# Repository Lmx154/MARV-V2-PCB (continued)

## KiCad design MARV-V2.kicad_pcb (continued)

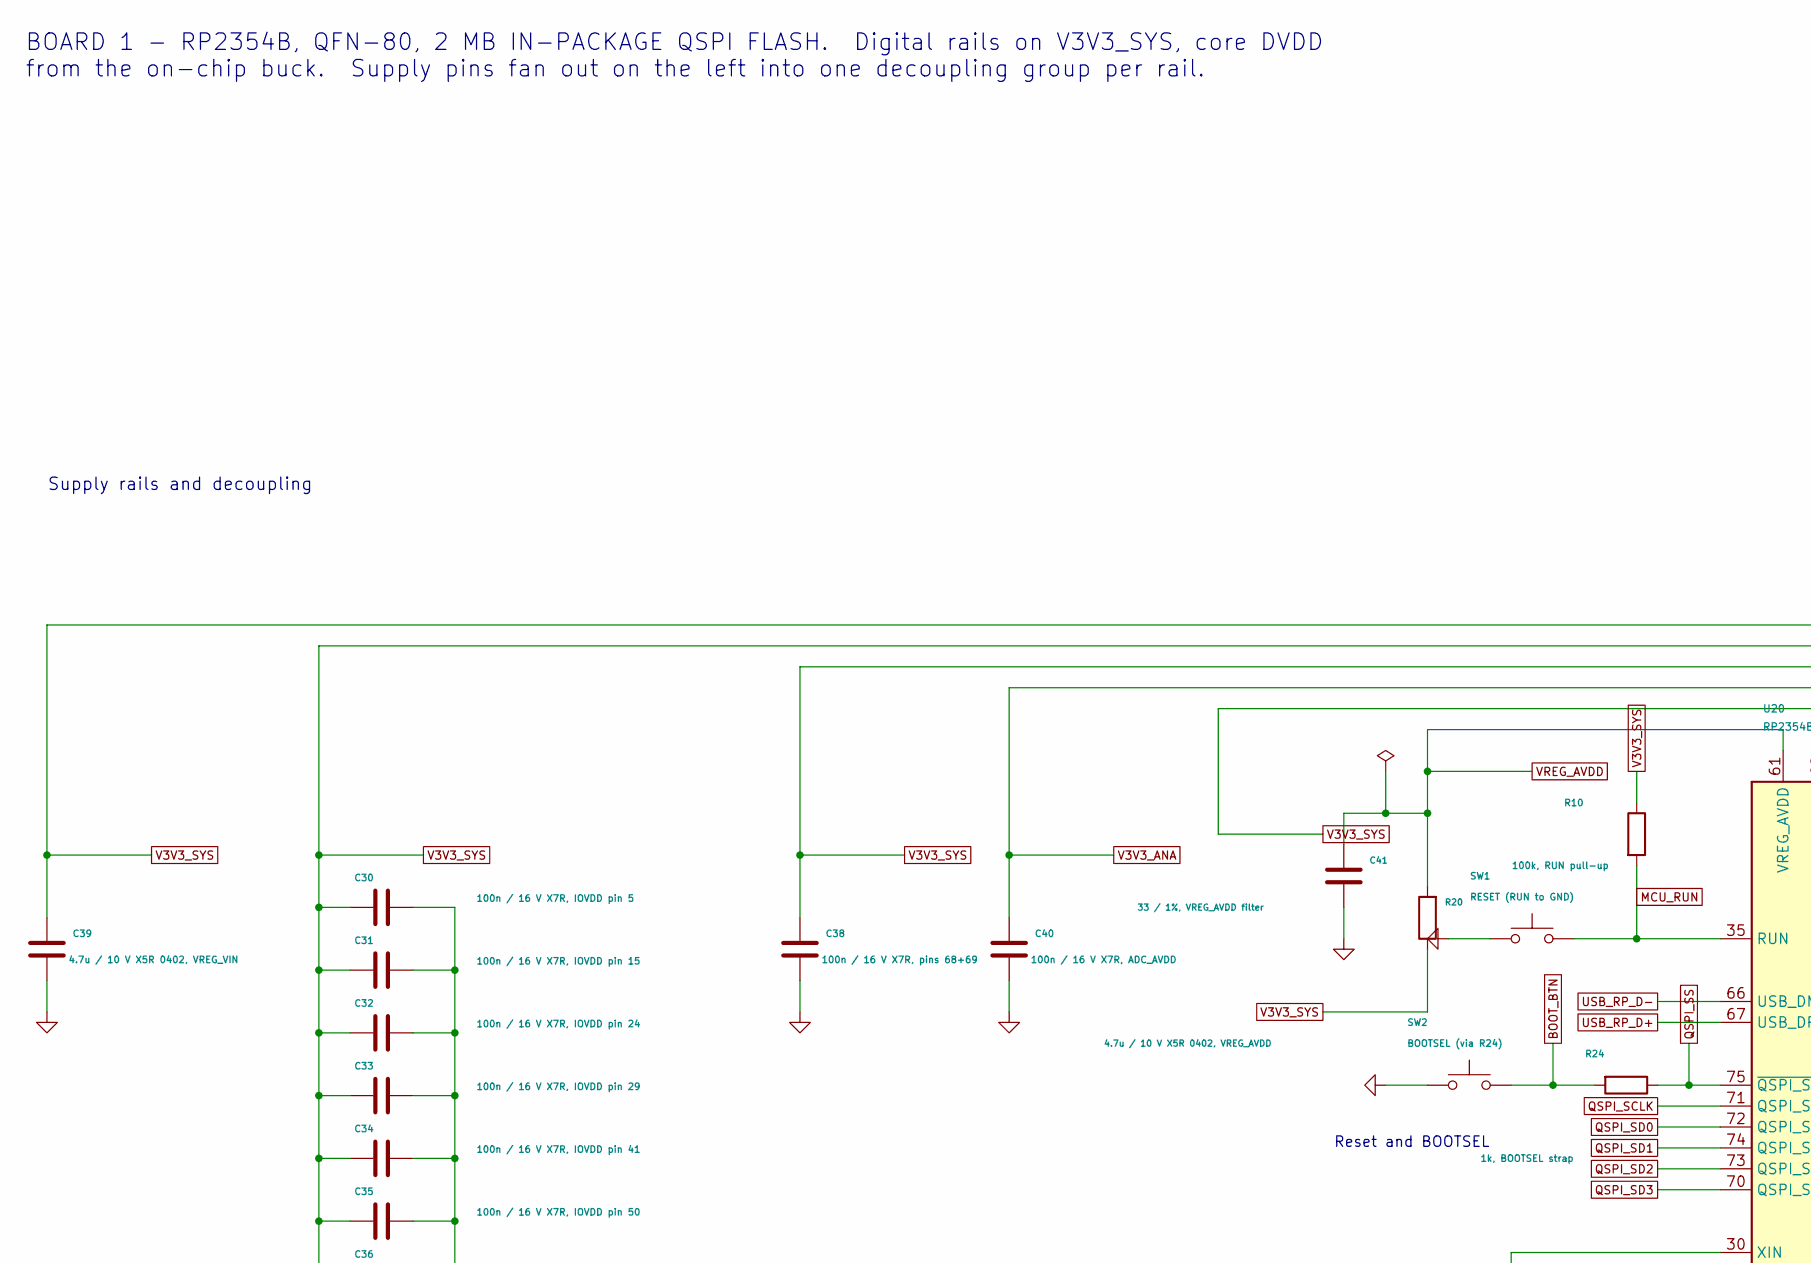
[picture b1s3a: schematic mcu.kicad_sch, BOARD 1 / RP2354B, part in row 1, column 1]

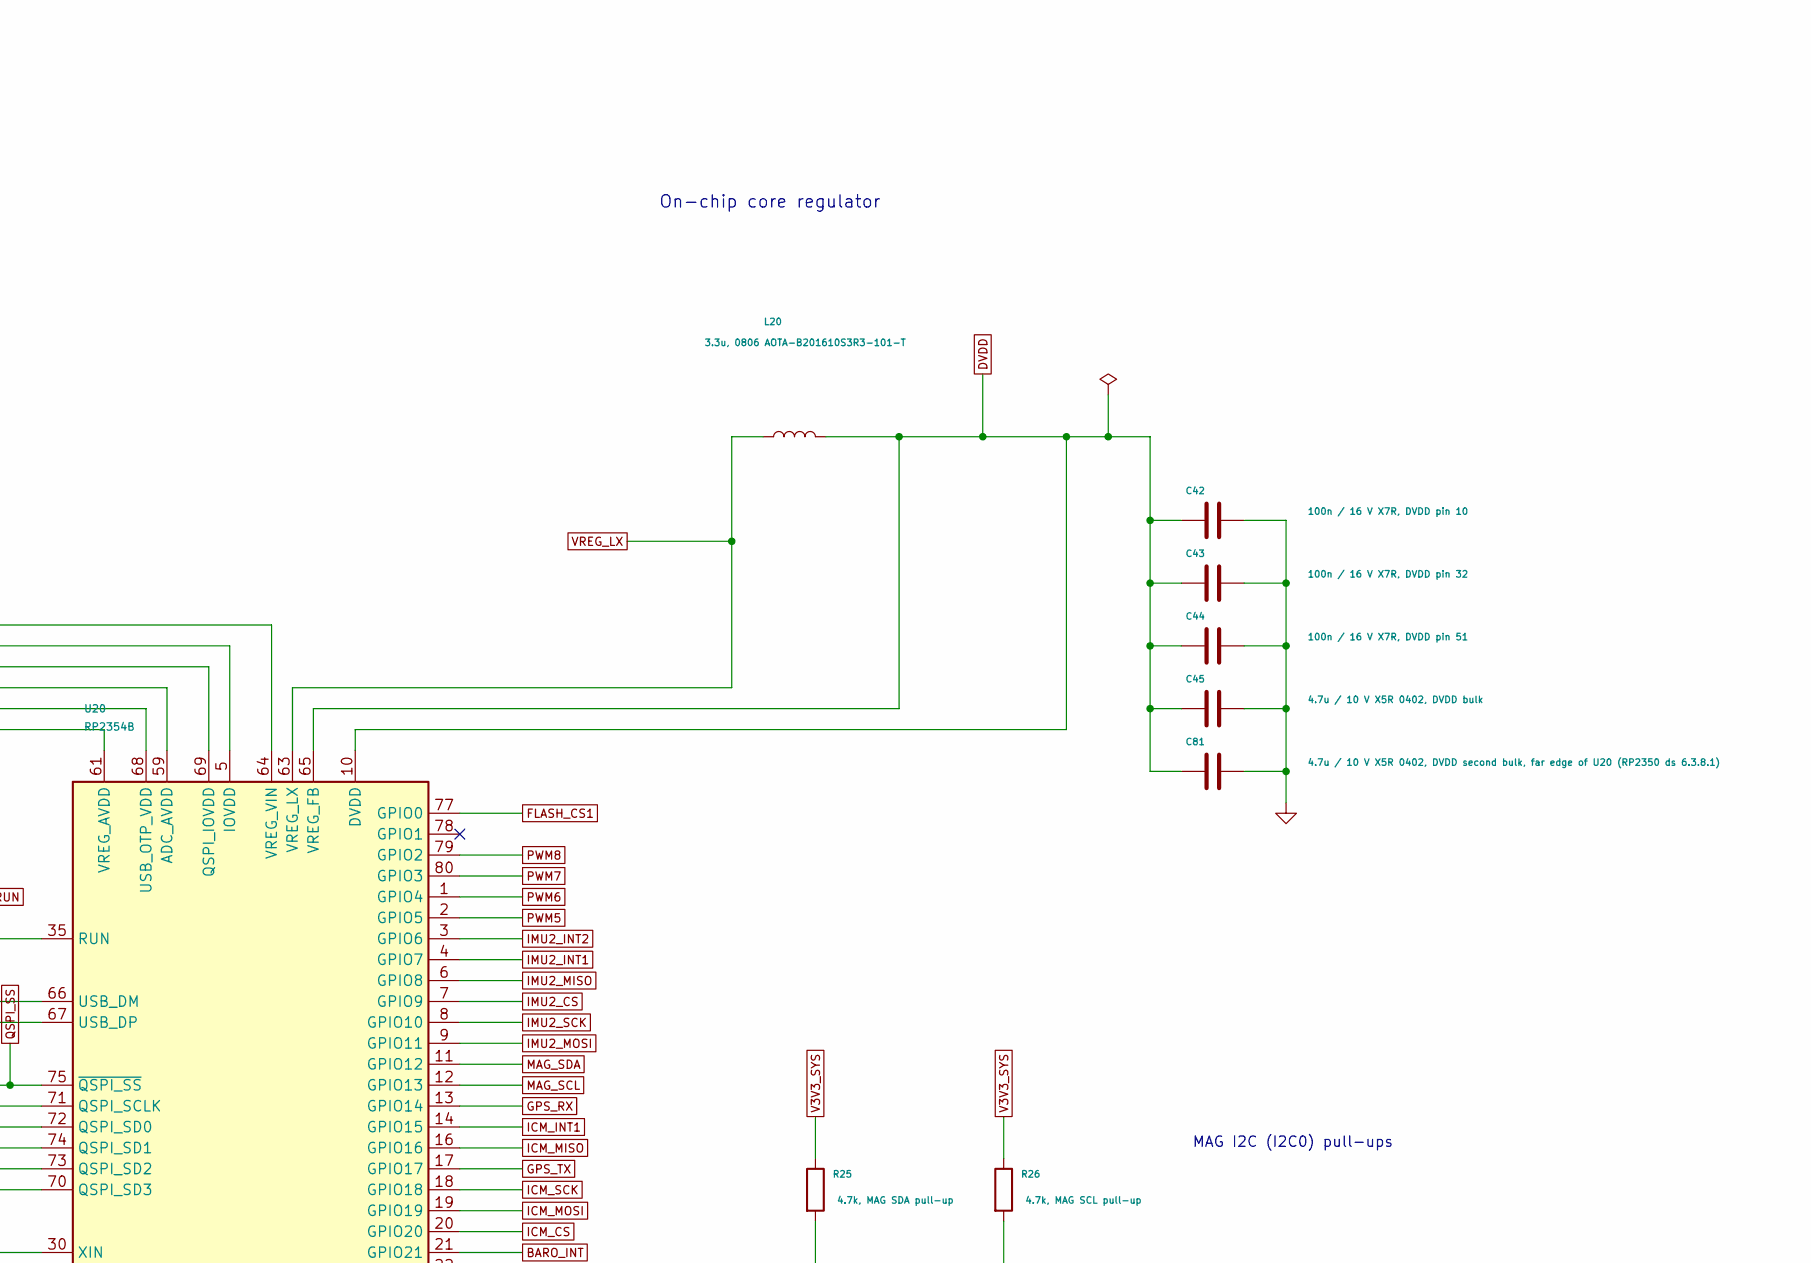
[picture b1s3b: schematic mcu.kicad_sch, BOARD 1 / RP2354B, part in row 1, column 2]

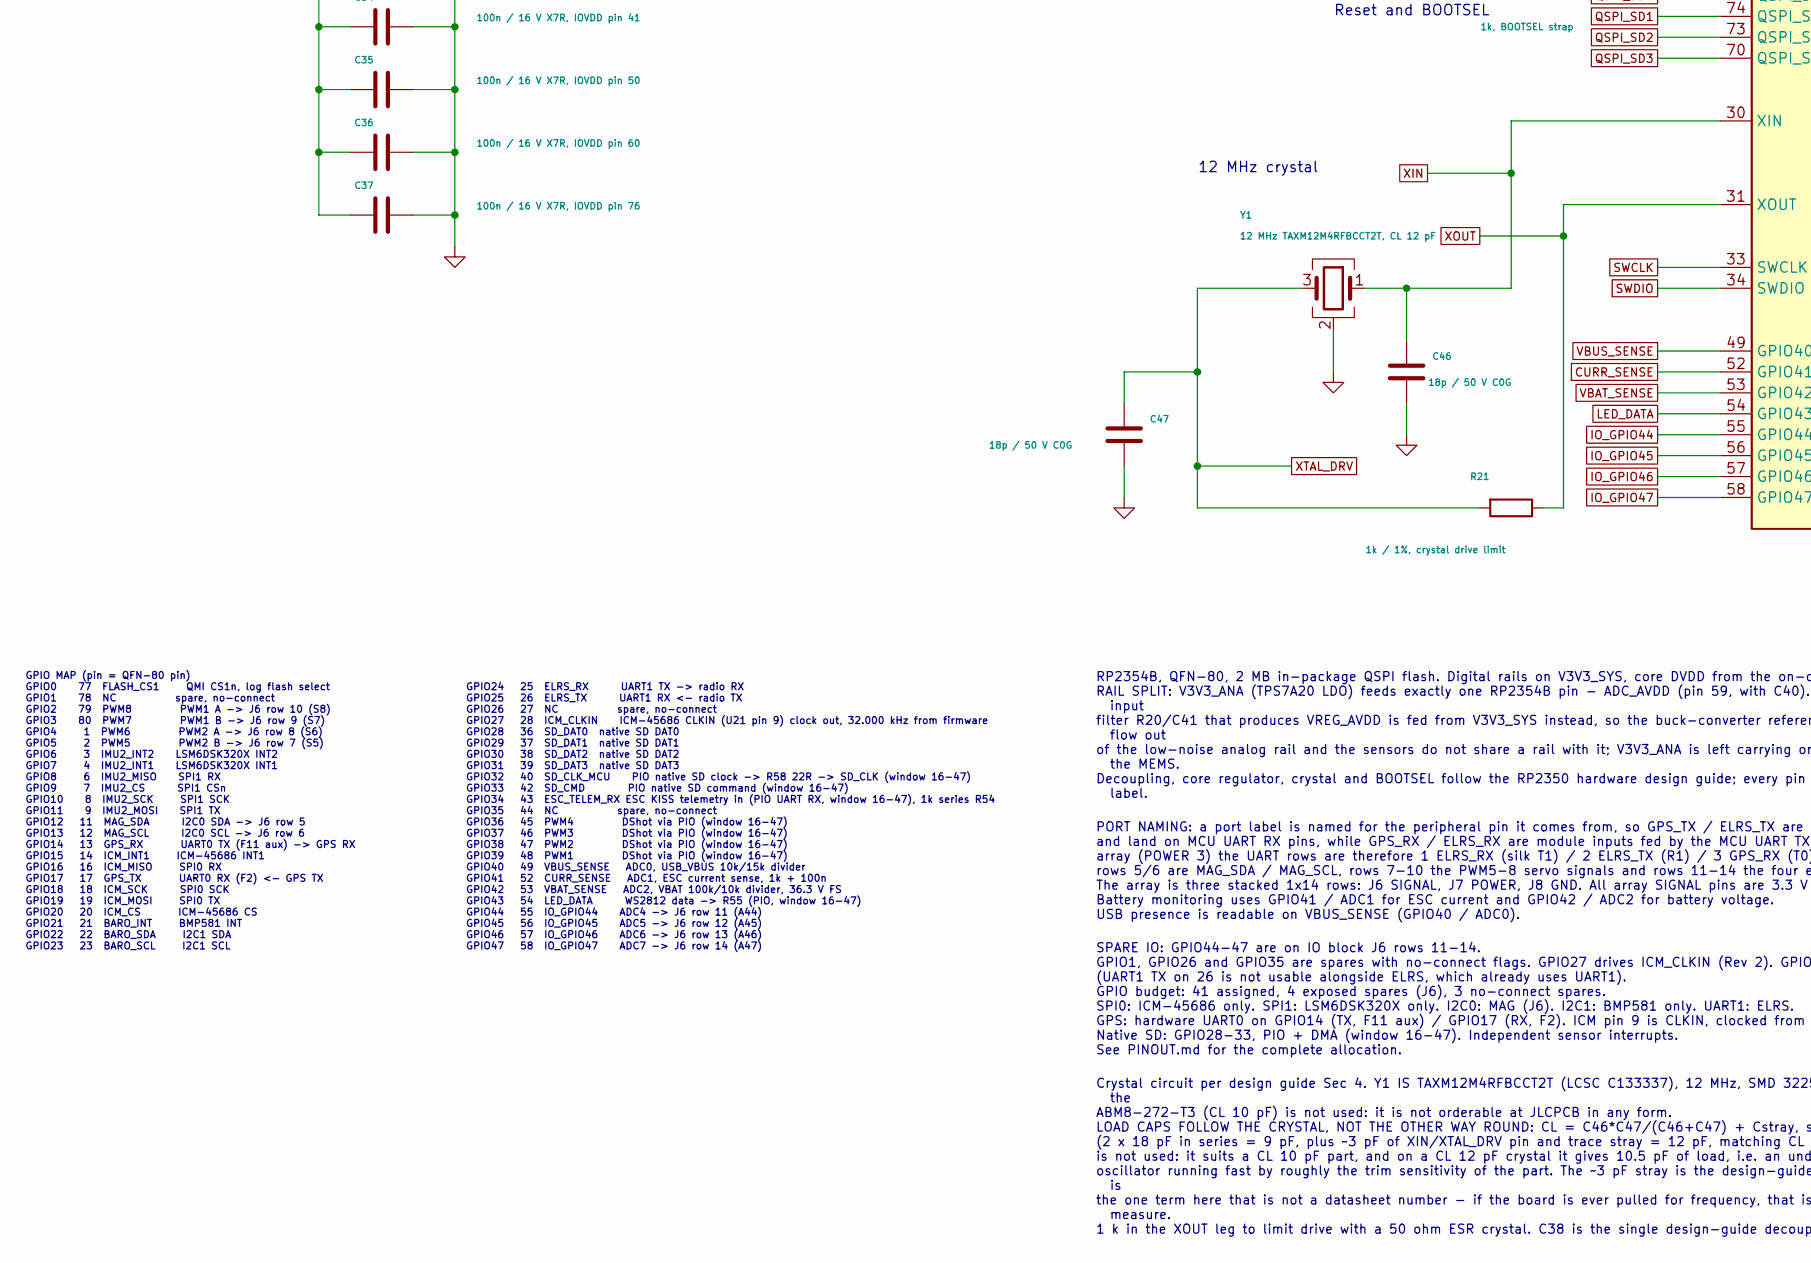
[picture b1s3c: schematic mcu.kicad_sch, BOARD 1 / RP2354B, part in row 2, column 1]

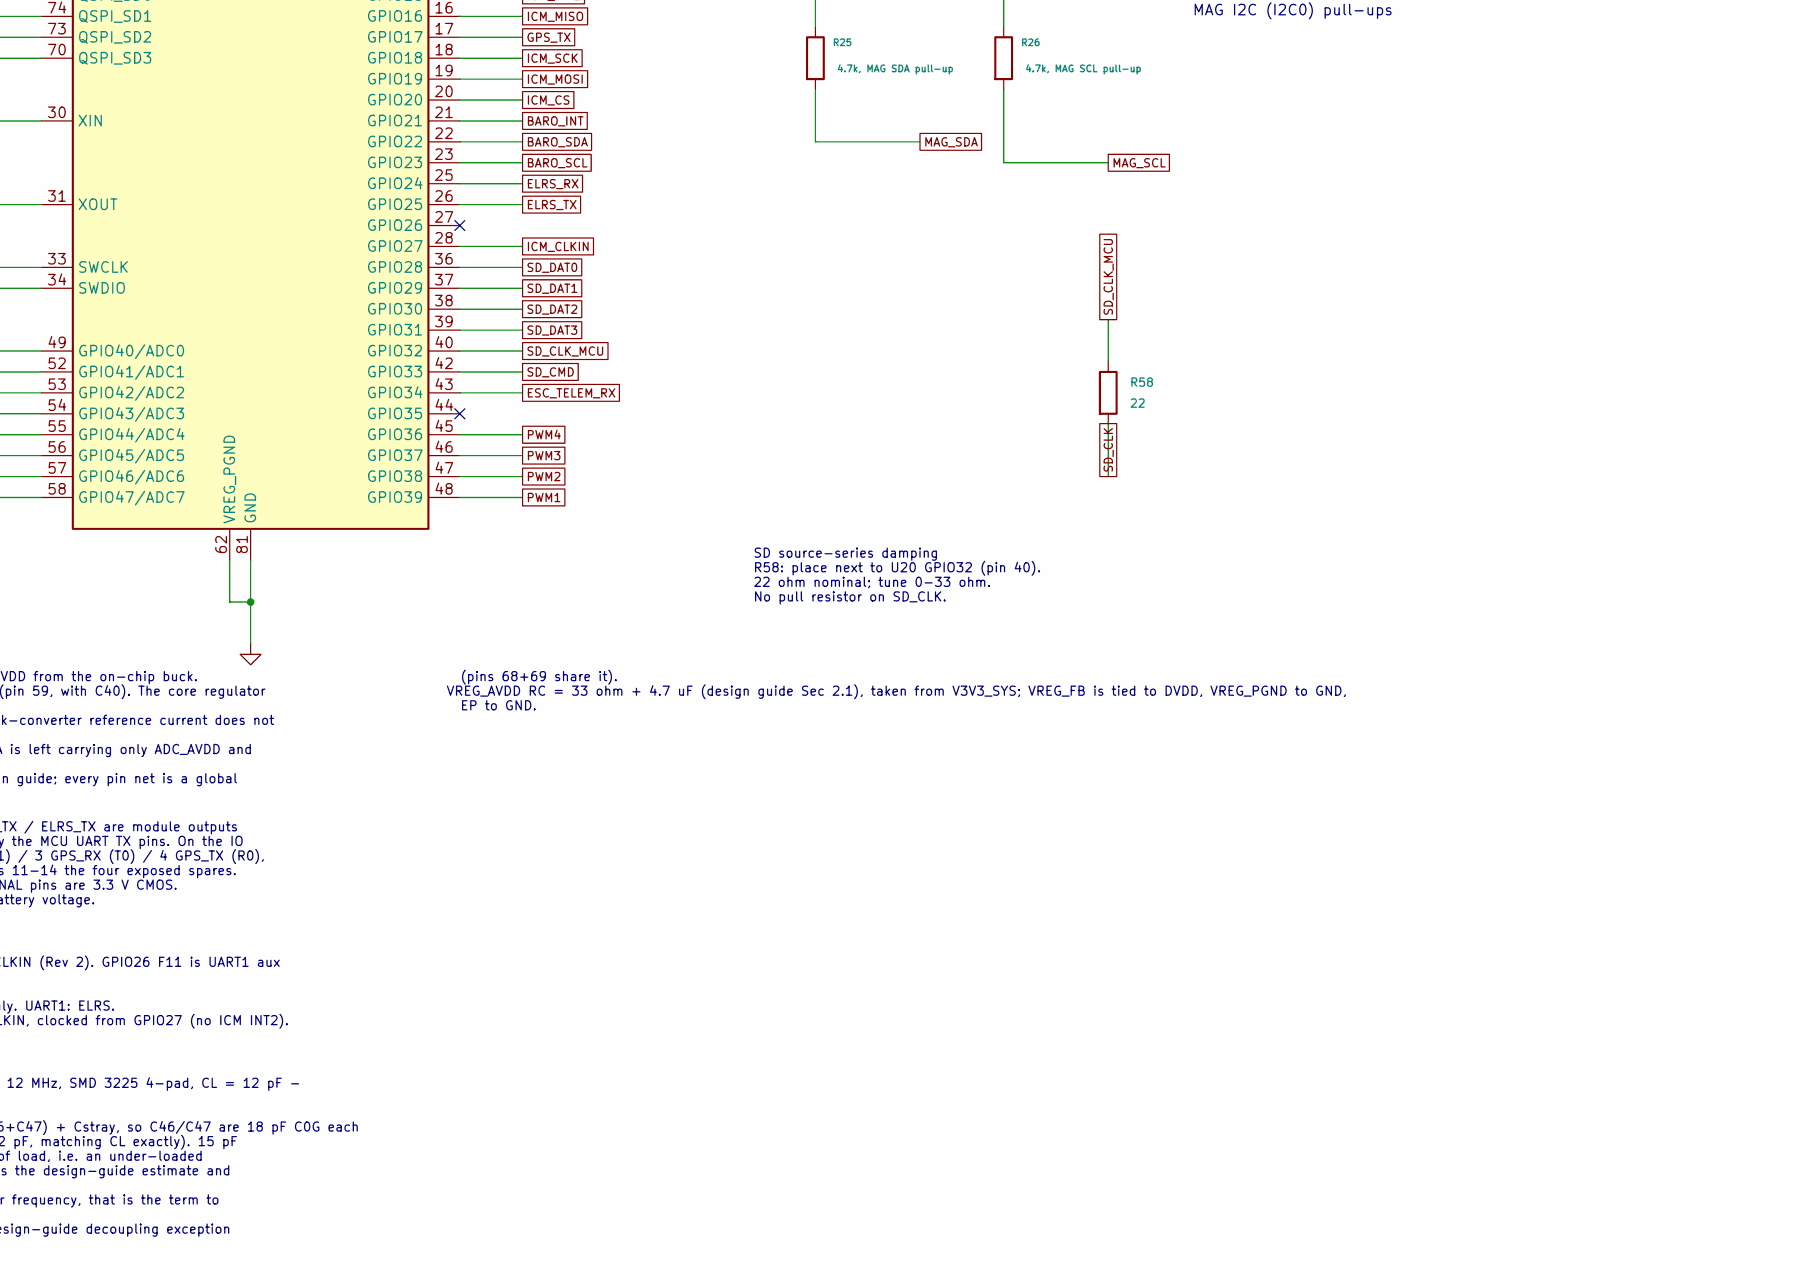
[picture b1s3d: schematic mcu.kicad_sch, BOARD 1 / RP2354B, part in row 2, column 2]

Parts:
C30: 100n / 16 V X7R, IOVDD pin 5; C_0402_1005Metric; LCSC C1525
C31: 100n / 16 V X7R, IOVDD pin 15; C_0402_1005Metric; LCSC C1525
C32: 100n / 16 V X7R, IOVDD pin 24; C_0402_1005Metric; LCSC C1525
C33: 100n / 16 V X7R, IOVDD pin 29; C_0402_1005Metric; LCSC C1525
C34: 100n / 16 V X7R, IOVDD pin 41; C_0402_1005Metric; LCSC C1525
C35: 100n / 16 V X7R, IOVDD pin 50; C_0402_1005Metric; LCSC C1525
C36: 100n / 16 V X7R, IOVDD pin 60; C_0402_1005Metric; LCSC C1525
C37: 100n / 16 V X7R, IOVDD pin 76; C_0402_1005Metric; LCSC C1525
C38: 100n / 16 V X7R, pins 68+69; C_0402_1005Metric; LCSC C1525
C39: 4.7u / 10 V X5R 0402, VREG_VIN; C_0402_1005Metric; LCSC C23733
C40: 100n / 16 V X7R, ADC_AVDD; C_0402_1005Metric; LCSC C1525
C41: 4.7u / 10 V X5R 0402, VREG_AVDD; C_0402_1005Metric; LCSC C23733
C42: 100n / 16 V X7R, DVDD pin 10; C_0402_1005Metric; LCSC C1525
C43: 100n / 16 V X7R, DVDD pin 32; C_0402_1005Metric; LCSC C1525
C44: 100n / 16 V X7R, DVDD pin 51; C_0402_1005Metric; LCSC C1525
C45: 4.7u / 10 V X5R 0402, DVDD bulk; C_0402_1005Metric; LCSC C23733
C46, C47: 18p / 50 V C0G; C_0402_1005Metric; LCSC C1549
C81: 4.7u / 10 V X5R 0402, DVDD second bulk, far edge 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; C_0402_1005Metric; LCSC C23733
L20: 3.3u, 0806 AOTA-B201610S3R3-101-T; L_Murata_DFE201610P; LCSC C42411119
R10: 100k, RUN pull-up; R_0402_1005Metric; LCSC C25741
R20: 33 / 1%, VREG_AVDD filter; R_0402_1005Metric; LCSC C25105
R21: 1k / 1%, crystal drive limit; R_0402_1005Metric; LCSC C11702
R24: 1k, BOOTSEL strap; R_0402_1005Metric; LCSC C11702
R25: 4.7k, MAG SDA pull-up; R_0402_1005Metric; LCSC C25900
R26: 4.7k, MAG SCL pull-up; R_0402_1005Metric; LCSC C25900
R58: 22; R_0402_1005Metric; LCSC C25092
SW1: RESET (RUN to GND); SW_SPST_B3U-1000P; LCSC C231329
SW2: BOOTSEL (via R24); SW_SPST_B3U-1000P; LCSC C231329
U20: RP2354B; QFN-80-1EP_10x10mm_P0.4mm_EP3.4x3.4mm; LCSC C39843328
Y1: 12 MHz TAXM12M4RFBCCT2T, CL 12 pF; Crystal_SMD_3225-4Pin_3.2x2.5mm; LCSC C133337

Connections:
BARO_INT: U20.21 (GPIO21); also elsewhere on the board
BARO_SCL: U20.23 (GPIO23); also elsewhere on the board
BARO_SDA: U20.22 (GPIO22); also elsewhere on the board
BOOT_BTN: R24.2, SW2.1
CURR_SENSE: U20.52 (GPIO41/ADC1); also elsewhere on the board
DVDD: C42.1, C43.1, C44.1, C45.1, C81.1, L20.2, U20.10 (DVDD), U20.32 (DVDD), U20.51 (DVDD), U20.65 (VREG_FB)
ELRS_RX: U20.25 (GPIO24); also elsewhere on the board
ELRS_TX: U20.26 (GPIO25); also elsewhere on the board
ESC_TELEM_RX: U20.43 (GPIO34); also elsewhere on the board
FLASH_CS1: U20.77 (GPIO0); also elsewhere on the board
GND: C30.2, C31.2, C32.2, C33.2, C34.2, C35.2, C36.2, C37.2, C38.2, C39.2, C40.2, C41.2, C42.2, C43.2, C44.2, C45.2, C46.2, C47.2, C81.2, SW1.2, SW2.2, U20.62 (VREG_PGND), U20.81 (GND), Y1.2 (G), Y1.4 (G); also elsewhere on the board
GPS_RX: U20.13 (GPIO14); also elsewhere on the board
GPS_TX: U20.17 (GPIO17); also elsewhere on the board
ICM_CLKIN: U20.28 (GPIO27); also elsewhere on the board
ICM_CS: U20.20 (GPIO20); also elsewhere on the board
ICM_INT1: U20.14 (GPIO15); also elsewhere on the board
ICM_MISO: U20.16 (GPIO16); also elsewhere on the board
ICM_MOSI: U20.19 (GPIO19); also elsewhere on the board
ICM_SCK: U20.18 (GPIO18); also elsewhere on the board
IMU2_CS: U20.7 (GPIO9); also elsewhere on the board
IMU2_INT1: U20.4 (GPIO7); also elsewhere on the board
IMU2_INT2: U20.3 (GPIO6); also elsewhere on the board
IMU2_MISO: U20.6 (GPIO8); also elsewhere on the board
IMU2_MOSI: U20.9 (GPIO11); also elsewhere on the board
IMU2_SCK: U20.8 (GPIO10); also elsewhere on the board
IO_GPIO44: U20.55 (GPIO44/ADC4); also elsewhere on the board
IO_GPIO45: U20.56 (GPIO45/ADC5); also elsewhere on the board
IO_GPIO46: U20.57 (GPIO46/ADC6); also elsewhere on the board
IO_GPIO47: U20.58 (GPIO47/ADC7); also elsewhere on the board
LED_DATA: U20.54 (GPIO43/ADC3); also elsewhere on the board
MAG_SCL: R26.2, U20.12 (GPIO13); also elsewhere on the board
MAG_SDA: R25.2, U20.11 (GPIO12); also elsewhere on the board
MCU_RUN: R10.2, SW1.1, U20.35 (RUN)
PWM1: U20.48 (GPIO39); also elsewhere on the board
PWM2: U20.47 (GPIO38); also elsewhere on the board
PWM3: U20.46 (GPIO37); also elsewhere on the board
PWM4: U20.45 (GPIO36); also elsewhere on the board
PWM5: U20.2 (GPIO5); also elsewhere on the board
PWM6: U20.1 (GPIO4); also elsewhere on the board
PWM7: U20.80 (GPIO3); also elsewhere on the board
PWM8: U20.79 (GPIO2); also elsewhere on the board
QSPI_SCLK: U20.71 (QSPI_SCLK); also elsewhere on the board
QSPI_SD0: U20.72 (QSPI_SD0); also elsewhere on the board
QSPI_SD1: U20.74 (QSPI_SD1); also elsewhere on the board
QSPI_SD2: U20.73 (QSPI_SD2); also elsewhere on the board
QSPI_SD3: U20.70 (QSPI_SD3); also elsewhere on the board
QSPI_SS: R24.1, U20.75 (~QSPI_SS)
SD_CLK: R58.2; also elsewhere on the board
SD_CLK_MCU: R58.1, U20.40 (GPIO32)
SD_CMD: U20.42 (GPIO33); also elsewhere on the board
SD_DAT0: U20.36 (GPIO28); also elsewhere on the board
SD_DAT1: U20.37 (GPIO29); also elsewhere on the board
SD_DAT2: U20.38 (GPIO30); also elsewhere on the board
SD_DAT3: U20.39 (GPIO31); also elsewhere on the board
SWCLK: U20.33 (SWCLK); also elsewhere on the board
SWDIO: U20.34 (SWDIO); also elsewhere on the board
USB_RP_D+: U20.67 (USB_DP); also elsewhere on the board
USB_RP_D-: U20.66 (USB_DM); also elsewhere on the board
V3V3_ANA: C40.1, U20.59 (ADC_AVDD); also elsewhere on the board
V3V3_SYS: C30.1, C31.1, C32.1, C33.1, C34.1, C35.1, C36.1, C37.1, C38.1, C39.1, R10.1, R20.1, R25.1, R26.1, U20.5 (IOVDD), U20.15 (IOVDD), U20.24 (IOVDD), U20.29 (IOVDD), U20.41 (IOVDD), U20.50 (IOVDD), U20.60 (IOVDD), U20.64 (VREG_VIN), U20.68 (USB_OTP_VDD), U20.69 (QSPI_IOVDD), U20.76 (IOVDD); also elsewhere on the board
VBAT_SENSE: U20.53 (GPIO42/ADC2); also elsewhere on the board
VBUS_SENSE: U20.49 (GPIO40/ADC0); also elsewhere on the board
VREG_AVDD: C41.1, R20.2, U20.61 (VREG_AVDD)
VREG_LX: L20.1, U20.63 (VREG_LX)
XIN: C46.1, U20.30 (XIN), Y1.1
XOUT: R21.1, U20.31 (XOUT)
XTAL_DRV: C47.1, R21.2, Y1.3

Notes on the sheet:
On-chip core regulator
Supply rails and decoupling
GPIO MAP (pin = QFN-80 pin) GPIO0 77 FLASH_CS1 QMI CS1n, log flash select GPIO1 78 NC spare, no-connect GPIO2 79 PWM8 PWM1 A -> J6 row 10 (S8) GPIO3 80 PWM7 PWM1 B -> J6 row 9 (S7) GPIO4 1 PWM6 PWM2 A -> J6 row 8 (S6) GPIO5 2 PWM5 PWM2 B -> J6 row 7 (S5) GPIO6 3 IMU2_INT2 LSM6DSK320X INT2 GPIO7 4 I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
PORT NAMING: a port label is named for the peripheral pin it comes from, so GPS_TX / ELRS_TX are module outputs and land on MCU UART RX pins, while GPS_RX / ELRS_RX are module inputs fed by the MCU UART TX pins. On the IO array (POWER 3) the UART rows are therefore 1 ELRS_RX (silk T1) / 2 ELRS_TX (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
MAG I2C (I2C0) pull-ups
BOARD 1 - RP2354B, QFN-80, 2 MB IN-PACKAGE QSPI FLASH. Digital rails on V3V3_SYS, core DVDD from the on-chip buck. Supply pins fan out on the left into one decoupling group per rail.
SPARE IO: GPIO44-47 are on IO block J6 rows 11-14. GPIO1, GPIO26 and GPIO35 are spares with no-connect flags. GPIO27 drives ICM_CLKIN (Rev 2). GPIO26 F11 is UART1 aux (UART1 TX on 26 is not usable alongside ELRS, which already uses UART1). GPIO budget: 41 assigned, 4 exposed spares (J6), 3 no-conne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
(pins 68+69 share it). VREG_AVDD RC = 33 ohm + 4.7 uF (design guide Sec 2.1), taken from V3V3_SYS; VREG_FB is tied to DVDD, VREG_PGND to GND, EP to GND.
SD source-series damping R58: place next to U20 GPIO32 (pin 40). 22 ohm nominal; tune 0-33 ohm. No pull resistor on SD_CLK.
Reset and BOOTSEL
12 MHz crystal
GPIO24 25 ELRS_RX UART1 TX -> radio RX GPIO25 26 ELRS_TX UART1 RX <- radio TX GPIO26 27 NC spare, no-connect GPIO27 28 ICM_CLKIN ICM-45686 CLKIN (U21 pin 9) clock out, 32.000 kHz from firmware GPIO28 36 SD_DAT0 native SD DAT0 GPIO29 37 SD_DAT1 native SD DAT1 GPIO30 38 SD_DAT2 native SD DAT2 GPIO31 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
RP2354B, QFN-80, 2 MB in-package QSPI flash. Digital rails on V3V3_SYS, core DVDD from the on-chip buck. RAIL SPLIT: V3V3_ANA (TPS7A20 LDO) feeds exactly one RP2354B pin - ADC_AVDD (pin 59, with C40). The core regulator input filter R20/C41 that produces VREG_AVDD is fed from V3V3_SYS instead, so t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
Crystal circuit per design guide Sec 4. Y1 IS TAXM12M4RFBCCT2T (LCSC C133337), 12 MHz, SMD 3225 4-pad, CL = 12 pF - the ABM8-272-T3 (CL 10 pF) is not used: it is not orderable at JLCPCB in any form. LOAD CAPS FOLLOW THE CRYSTAL, NOT THE OTHER WAY ROUND: CL = C46*C47/(C46+C47) + Cstray, so C46/C47 a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

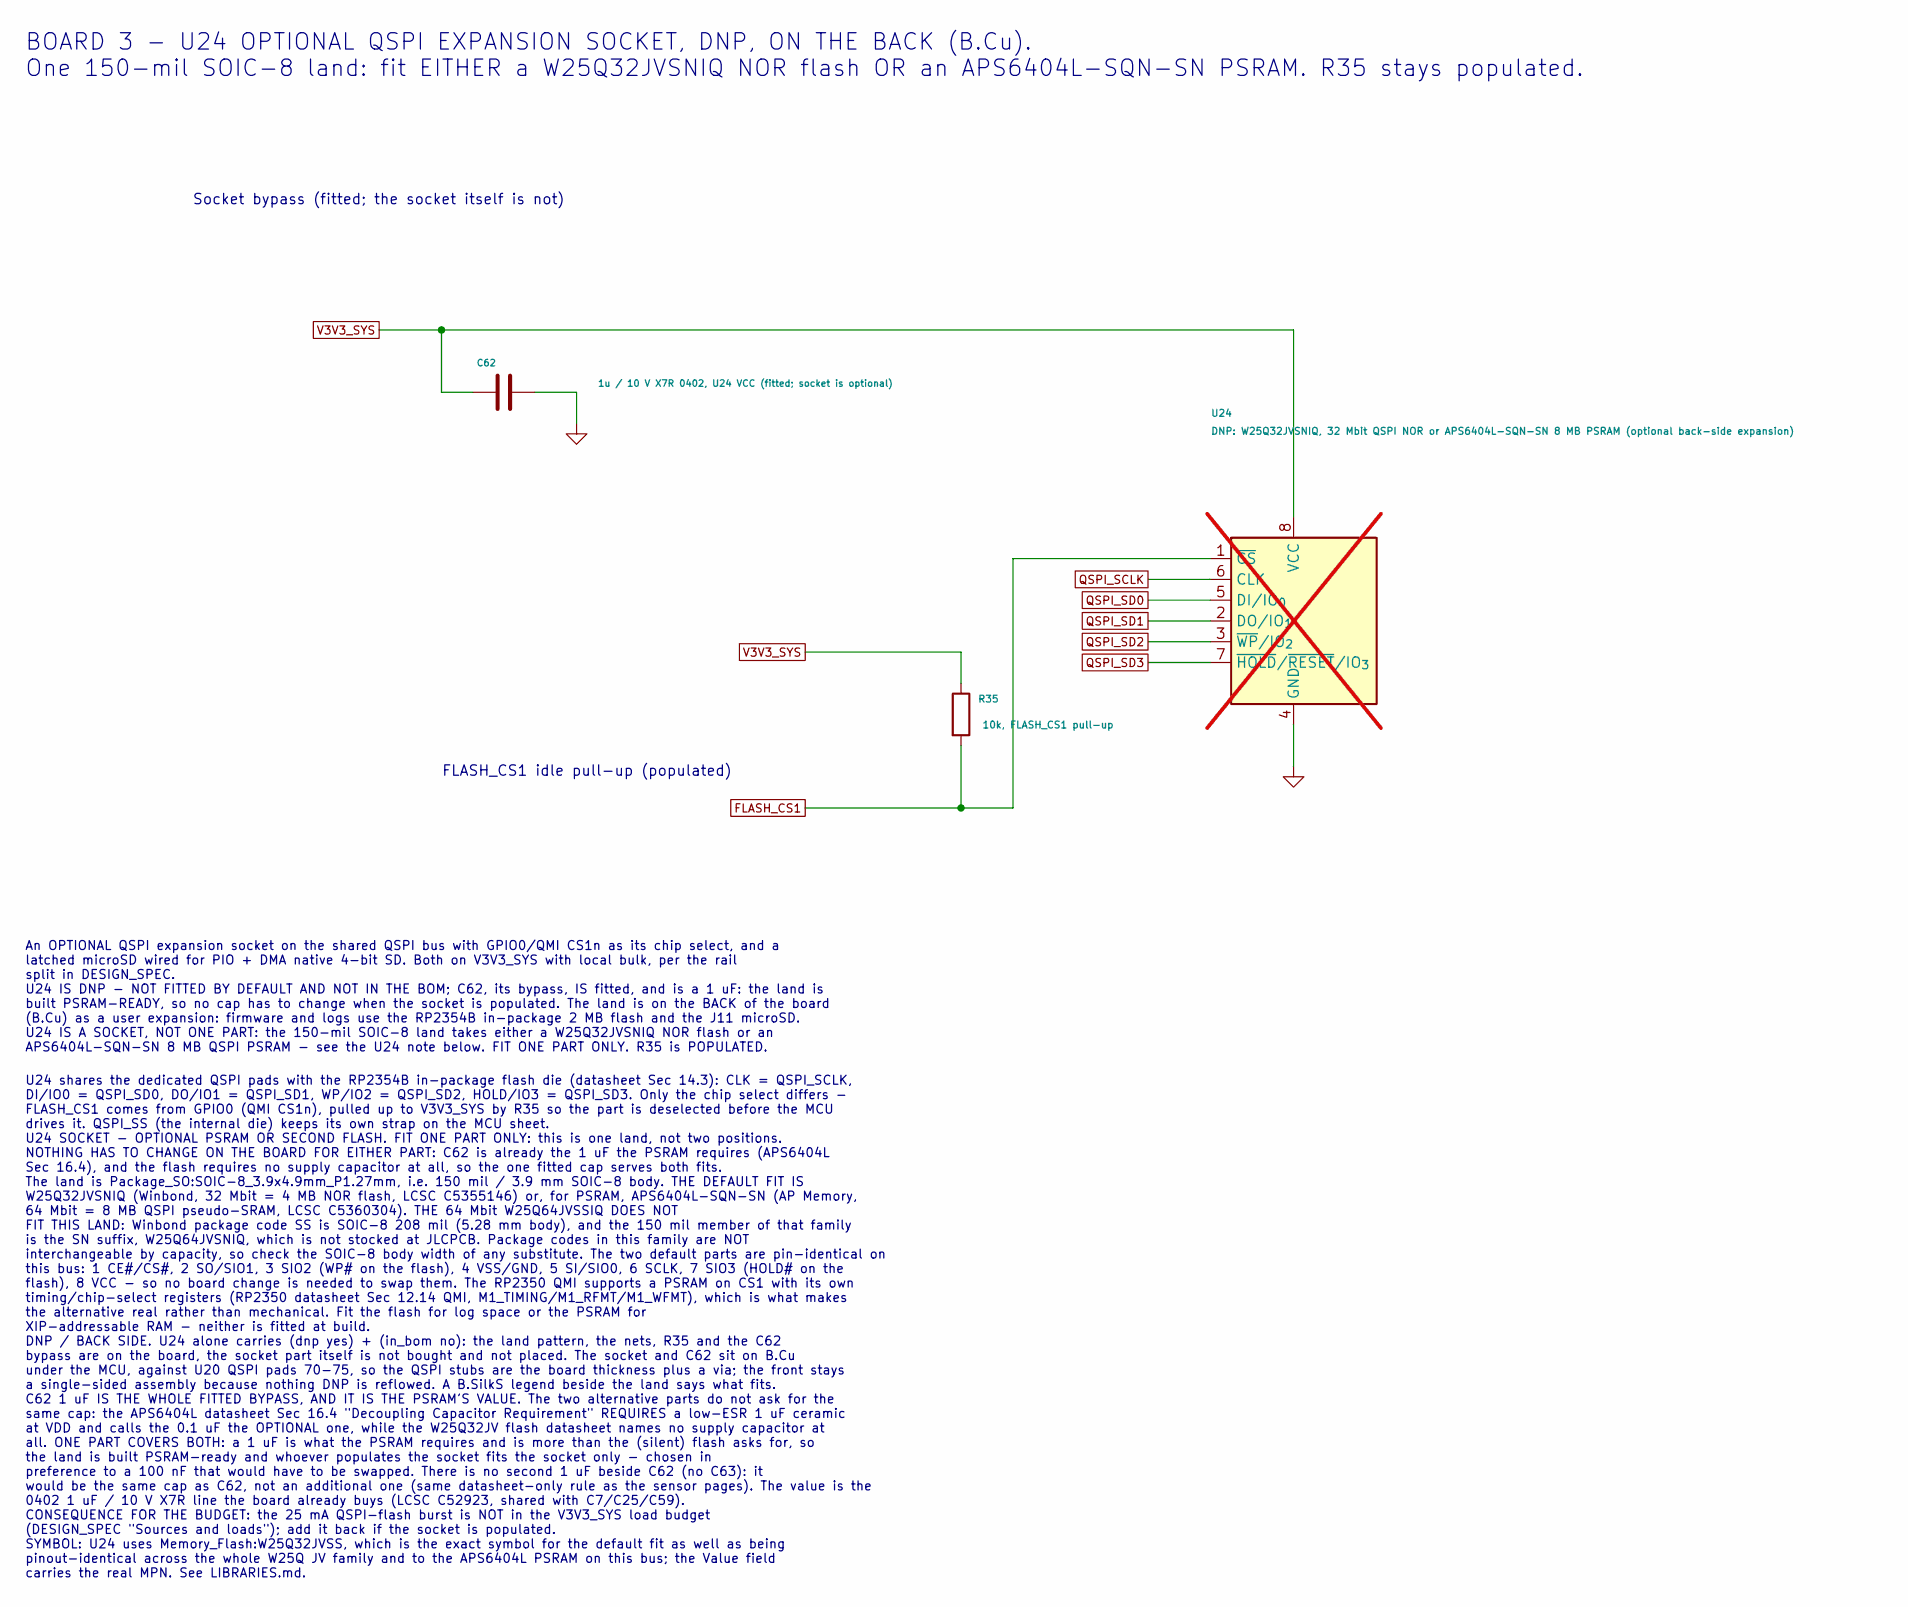
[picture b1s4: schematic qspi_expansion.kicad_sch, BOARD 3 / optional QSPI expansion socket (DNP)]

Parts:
C62: 1u / 10 V X7R 0402, U24 VCC (fitted; socket is op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; C_0402_1005Metric; LCSC C52923
R35: 10k, FLASH_CS1 pull-up; R_0402_1005Metric; LCSC C25744
U24: DNP: W25Q32JVSNIQ, 32 Mbit QSPI NOR or APS6404L-S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; SOIC-8_3.9x4.9mm_P1.27mm; not fitted

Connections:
FLASH_CS1: R35.2, U24.1 (~CS); also elsewhere on the board
GND: C62.2, U24.4 (GND); also elsewhere on the board
QSPI_SCLK: U24.6 (CLK); also elsewhere on the board
QSPI_SD0: U24.5 (DI/IO_{0}); also elsewhere on the board
QSPI_SD1: U24.2 (DO/IO_{1}); also elsewhere on the board
QSPI_SD2: U24.3 (~WP/IO_{2}); also elsewhere on the board
QSPI_SD3: U24.7 (~HOLD/~RESET/IO_{3}); also elsewhere on the board
V3V3_SYS: C62.1, R35.1, U24.8 (VCC); also elsewhere on the board

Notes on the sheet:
FLASH_CS1 idle pull-up (populated)
An OPTIONAL QSPI expansion socket on the shared QSPI bus with GPIO0/QMI CS1n as its chip select, and a latched microSD wired for PIO + DMA native 4-bit SD. Both on V3V3_SYS with local bulk, per the rail split in DESIGN_SPEC. U24 IS DNP - NOT FITTED BY DEFAULT AND NOT IN THE BOM; C62, its bypass, IS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
Socket bypass (fitted; the socket itself is not)
BOARD 3 - U24 OPTIONAL QSPI EXPANSION SOCKET, DNP, ON THE BACK (B.Cu). One 150-mil SOIC-8 land: fit EITHER a W25Q32JVSNIQ NOR flash OR an APS6404L-SQN-SN PSRAM. R35 stays populated.
U24 shares the dedicated QSPI pads with the RP2354B in-package flash die (datasheet Sec 14.3): CLK = QSPI_SCLK, DI/IO0 = QSPI_SD0, DO/IO1 = QSPI_SD1, WP/IO2 = QSPI_SD2, HOLD/IO3 = QSPI_SD3. Only the chip select differs - FLASH_CS1 comes from GPIO0 (QMI CS1n), pulled up to V3V3_SYS by R35 so the par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
